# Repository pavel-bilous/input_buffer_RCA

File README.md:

# RCA input buffer

Impedance matching buffer that converts RCA inputs into balanced signal.

## PCB rendered in 3d:

## Schematics:

Inputs are ESD protected with bidirectional TVS diodes. Not required, but nice to have. 

Opamps can be NE5532 or LM4562 or any other with good unity gain stability. 

Input XLR connectors are Neutrik NC3FAAH2.

Capacitors for input low pass filters are film type. Decoupling capacitors are X7R 100nF or higher (1uF - 10uF will work great).

## PCB layout:

Bottom layer is GND. Top layer is signal + power and GND poured in between. Stiching vias are then applied to connect bottom and top GND planes to ensure those are as close to 0 as possible.

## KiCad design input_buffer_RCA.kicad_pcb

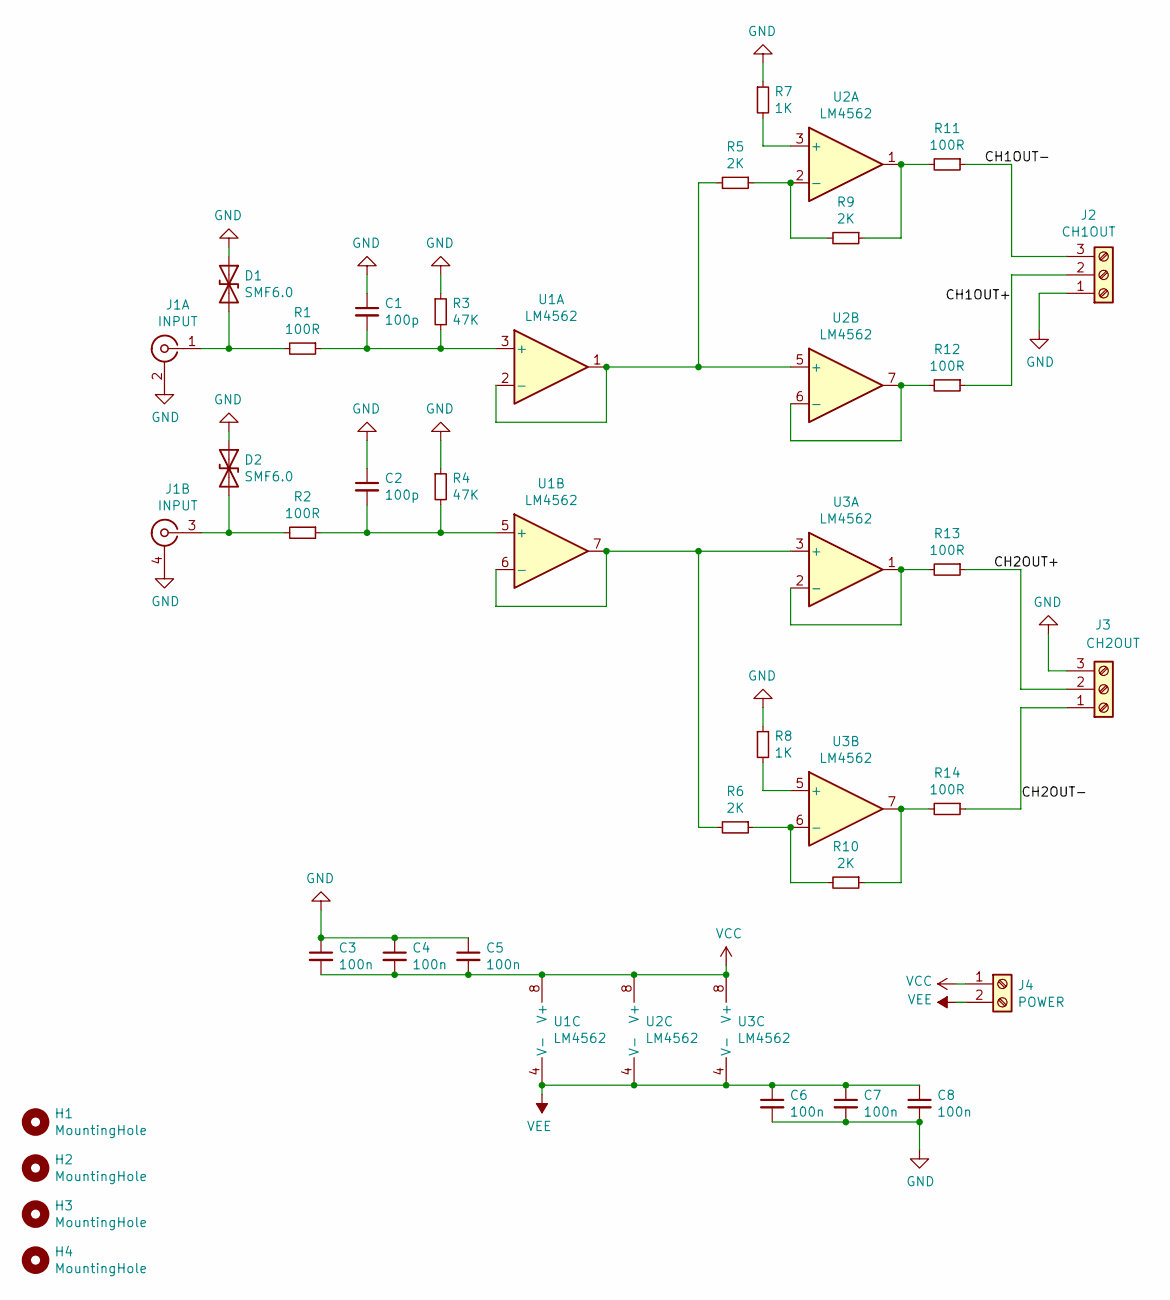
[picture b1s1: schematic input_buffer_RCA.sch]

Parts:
C1, C2: 100p; C_1206_3216Metric_Pad1.42x1.75mm_HandSolder
C3, C4, C5, C6, C7, C8: 100n; C_1206_3216Metric_Pad1.42x1.75mm_HandSolder
D1, D2: SMF6.0; D_SOD-123F
H1, H2, H3, H4: MountingHole; MountingHole_3.2mm_M3_Pad_Via
J1: INPUT; RCA_Switchcraft_PJRAS2X1S01X
J2: CH1OUT; TerminalBlock_ Amphenol_01_03_P3.50mm
J3: CH2OUT; TerminalBlock_ Amphenol_01_03_P3.50mm
J4: POWER; TerminalBlock_ Amphenol_01_02_P3.50mm
R1, R2, R11, R12, R13, R14: 100R; R_1206_3216Metric_Pad1.42x1.75mm_HandSolder
R3, R4: 47K; R_1206_3216Metric_Pad1.42x1.75mm_HandSolder
R5, R6, R9, R10: 2K; R_1206_3216Metric_Pad1.42x1.75mm_HandSolder
R7, R8: 1K; R_1206_3216Metric_Pad1.42x1.75mm_HandSolder
U1, U2, U3: LM4562; SOIC-8_3.9x4.9mm_P1.27mm

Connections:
/CH1OUT+: J2.2, R12.1
/CH1OUT-: J2.3, R11.1
/CH2OUT+: J3.2, R13.1
/CH2OUT-: J3.1, R14.1
GND: C1.1, C2.1, C3.1, C4.1, C5.1, C6.2, C7.2, C8.2, D1.1 (A1), D2.1 (A1), J1.2 (Ext1), J1.4 (Ext2), J2.1, J3.3, R3.1, R4.1, R7.1, R8.1
unnamed: C1.2, R1.1, R3.2, U1.3 (+)
unnamed: C2.2, R2.1, R4.2, U1.5 (+)
unnamed: D1.2 (A2), J1.1 (In1), R1.2
unnamed: D2.2 (A2), J1.3 (In2), R2.2
unnamed: R5.1, R9.2, U2.2 (-)
unnamed: R5.2, U1.1, U1.2 (-), U2.5 (+)
unnamed: R6.2, U1.6 (-), U1.7, U3.3 (+)
unnamed: R7.2, U2.3 (+)
unnamed: R8.2, U3.5 (+)
unnamed: R10.1, R14.2, U3.7
unnamed: R6.1, R10.2, U3.6 (-)
unnamed: R9.1, R11.2, U2.1
unnamed: R12.2, U2.6 (-), U2.7
unnamed: R13.2, U3.1, U3.2 (-)
VCC: C3.2, C4.2, C5.2, J4.1, U1.8 (V+), U2.8 (V+), U3.8 (V+)
VEE: C6.1, C7.1, C8.1, J4.2, U1.4 (V-), U2.4 (V-), U3.4 (V-)

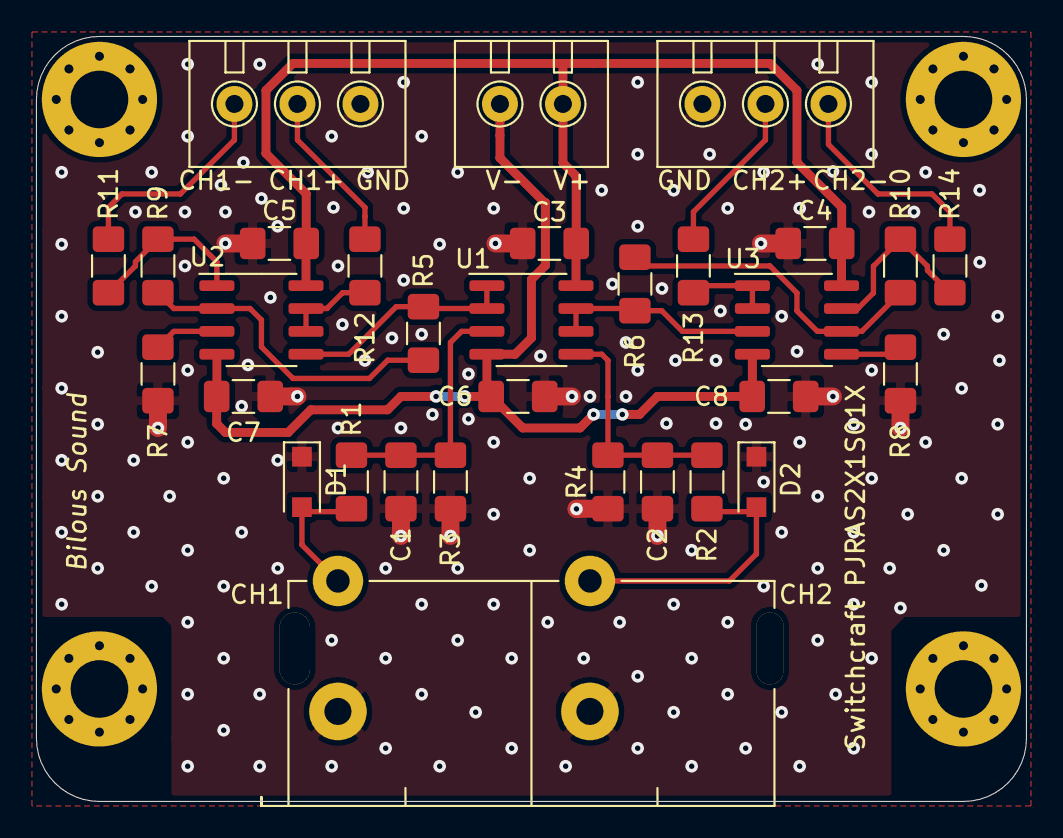
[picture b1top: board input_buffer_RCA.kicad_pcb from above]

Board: 2 copper layers, 55.0 x 42.5 mm, 35 parts (0 on the bottom side), 21 nets.

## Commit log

2023-05-11 minor changes
2023-05-12 rearranged components to reduce board size
2023-06-01 rev2
